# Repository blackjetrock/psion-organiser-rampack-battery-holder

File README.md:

# psion-organiser-rampack-battery-holder
Battery holder PCB for Psion Organiser II RAM packs

This is a PCB that can be attached to a Psion Organiser II RAM pack in place of the soldered in battery that was originally fitted. It has a 2032 type battery holder mounted on it that holds a 2032 battery. This makes the battery easily replaceable, much easier than unsoldering the original, sourcing a battery that will fit the PCB and soldering that in.

You will need to find a battery holder that fits the PCB footprint. The ones I found were actually through-hole parts but it's easy to bend the tabs and turn them into surface mount. They are also too big to fit in the standard datapack case so I had to sand away the sides until they fitted using a disc sander.

Fitting the PCB isn't the easiest of tasks, due to a number of difficulties.

Here's a rough sequence:

1. Test that the RAM pack still works. battery leakage can cause corrosion that destroys the tracks on the PCB and even the ICs
2. Fix the RAM pack if possible. If it still doesn't work then it's the end of the pack...

3. Cut the original battery off    (easy)
4. Clear the battery wire holes of solder (hard)
   I've used a vacuum desoldering tool for this, but it's still difficult to do for some reason.
5. Solder wires into the PCB holes
6. File, sand, cut the wire and solder that sits under the battery. This joint needs to be perfectly smooth otherwise the battery won't slide into the holder. Unfortunately you have to reheat this joint when soldering the PCB on the datapack so either solder that joint quickly or fit the battery holder after filing. If you fit after filing though, be careful not to get filing over the PCBs as it is conductive.
7. Place modified battery holder on PCB and solder it. Soilder the joints quickly to avoid melting the first joints or the wires will fall out of the PCB and you have to start again.
8 Check battery slides into holder
9. Check case fits.
10. Check RAM pack works and retains contenets after removed from organiser.

It's involved and quite time consuming but it can be done. There's videos here:

https://www.youtube.com/watch?v=c5Nr7drKGiE

https://www.youtube.com/watch?v=4RJYu7aHiQ8

https://www.youtube.com/watch?v=rGJUii9sP6A

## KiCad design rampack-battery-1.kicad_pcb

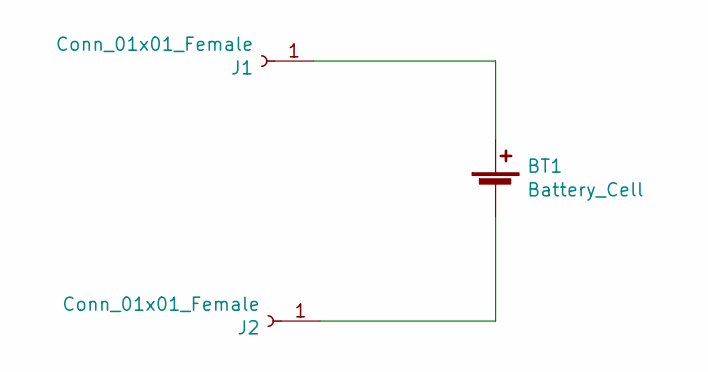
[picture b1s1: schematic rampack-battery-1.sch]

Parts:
BT1: Battery_Cell; BatteryHolder_MPD_BC2003_1x2032
J1, J2: Conn_01x01_Female; PinHeader_1x01_P2.54mm_Vertical

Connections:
unnamed: BT1.1 (+), J1.1
unnamed: BT1.2 (-), J2.1

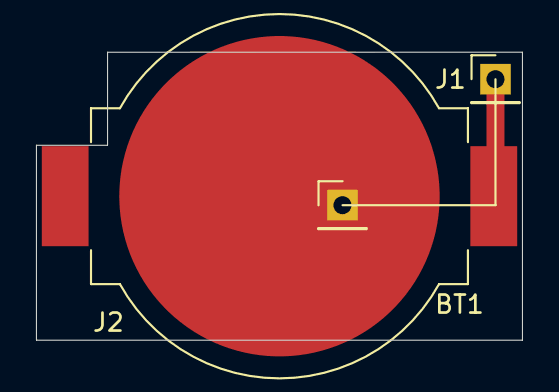
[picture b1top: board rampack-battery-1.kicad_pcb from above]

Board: 2 copper layers, 27.0 x 16.0 mm, 3 parts (0 on the bottom side), 2 nets.
